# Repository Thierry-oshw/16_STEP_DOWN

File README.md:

# 16_STEP_DOWN
 STED DOWN DCDC converter 7V-32V

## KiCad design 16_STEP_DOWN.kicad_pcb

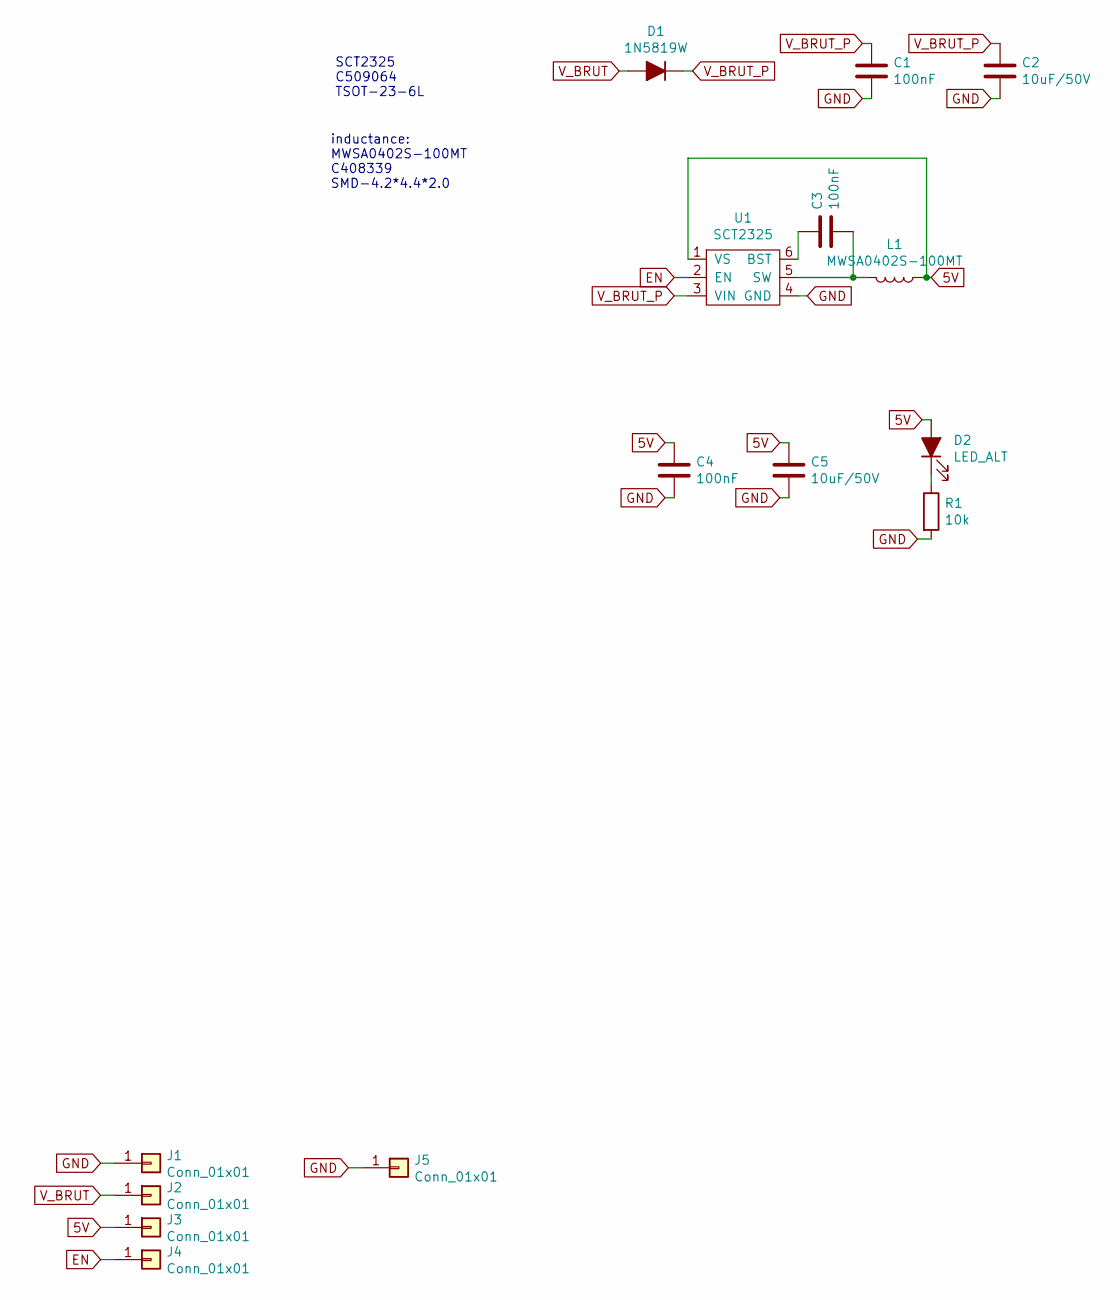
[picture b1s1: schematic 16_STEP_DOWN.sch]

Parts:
C1, C3, C4: 100nF; C_0603_1608Metric
C2, C5: 10uF/50V; C_1210_3225Metric
D1: 1N5819W; D_SOD-123F
D2: LED_ALT; D_0603_1608Metric
J1, J2, J3, J4, J5: Conn_01x01; Castellated_conn
L1: MWSA0402S-100MT; L_Sunlord_MWSA0402S_4.2x4.4x2.0mm
R1: 10k; R_0603_1608Metric
U1: SCT2325; TSOT-23-6_HandSoldering

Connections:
5V: C4.1, C5.1, D2.2 (A), J3.1, L1.1, U1.1 (VS)
EN: J4.1, U1.2 (EN)
GND: C1.2, C2.2, C4.2, C5.2, J1.1, J5.1, R1.2, U1.4 (GND)
unnamed: C3.1, U1.6 (BST)
unnamed: C3.2, L1.2, U1.5 (SW)
unnamed: D2.1 (K), R1.1
V_BRUT: D1.2 (A), J2.1
V_BRUT_P: C1.1, C2.1, D1.1 (K), U1.3 (VIN)

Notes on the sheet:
SCT2325 C509064 TSOT-23-6L
inductance: MWSA0402S-100MT C408339 SMD-4.2*4.4*2.0

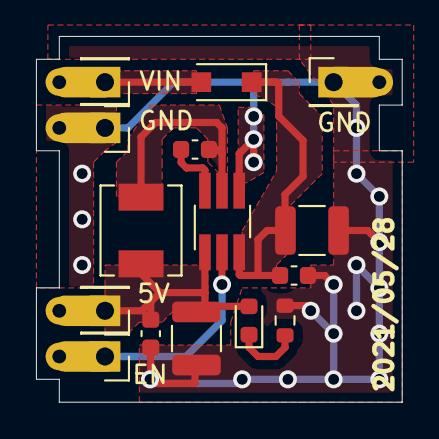
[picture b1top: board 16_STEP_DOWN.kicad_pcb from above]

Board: 2 copper layers, 20.3 x 20.3 mm, 15 parts (0 on the bottom side), 8 nets.

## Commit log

2021-05-27 creation
    sauvegarde du travail en cours; parti de la carte XCAN
2021-05-28 prêt pour fabrication
    ajout sct2325
    routage
2021-07-26 maj split librairies
2023-05-02 chgt nom fichier licence
